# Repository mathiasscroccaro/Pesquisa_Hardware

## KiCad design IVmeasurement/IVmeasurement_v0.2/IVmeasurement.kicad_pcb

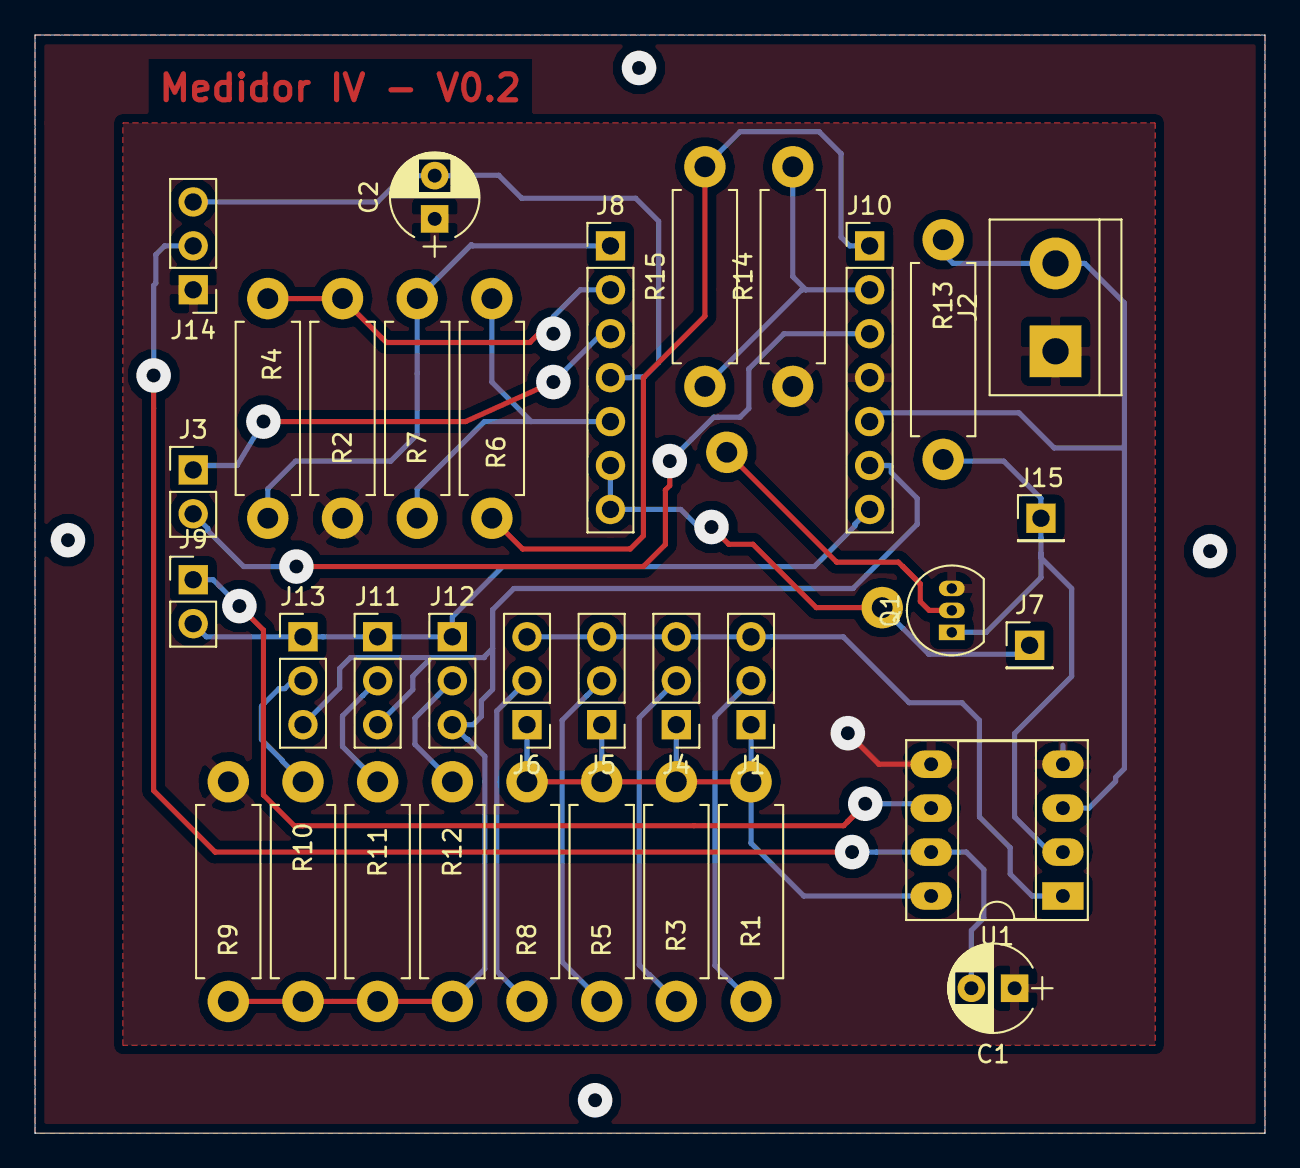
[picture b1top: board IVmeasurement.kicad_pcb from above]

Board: 2 copper layers, 71.1 x 63.5 mm, 35 parts (1 on the bottom side), 26 nets.

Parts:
C1, C2: 100nF; CP_Radial_D5.0mm_P2.50mm
J1, J4, J5, J6, J11, J12, J13: Conn_01x03; Pin_Header_Straight_1x03_Pitch2.54mm
J2: Sollar Cell; TerminalBlock_bornier-2_P5.08mm
J3: DAC; Pin_Header_Straight_1x02_Pitch2.54mm
J7: Test VGS; Pin_Header_Straight_1x01_Pitch2.54mm
J8, J10: Conn_01x07; Pin_Header_Straight_1x07_Pitch2.54mm
J9: ADC; Pin_Header_Straight_1x02_Pitch2.54mm
J14: Source; Pin_Header_Straight_1x03_Pitch2.54mm
J15: Test VDS; Pin_Header_Straight_1x01_Pitch2.54mm
Q1: BS170; TO-92_Inline_Narrow_Oval
R1, R6: 1M; R_Axial_DIN0411_L9.9mm_D3.6mm_P12.70mm_Horizontal
R2, R7, R14: 100k; R_Axial_DIN0411_L9.9mm_D3.6mm_P12.70mm_Horizontal
R3: 7.1k; R_Axial_DIN0411_L9.9mm_D3.6mm_P12.70mm_Horizontal
R4, R15: 51k; R_Axial_DIN0411_L9.9mm_D3.6mm_P12.70mm_Horizontal
R5: 609; R_Axial_DIN0411_L9.9mm_D3.6mm_P12.70mm_Horizontal
R8: 60; R_Axial_DIN0411_L9.9mm_D3.6mm_P12.70mm_Horizontal
R9: 10k; R_Axial_DIN0411_L9.9mm_D3.6mm_P12.70mm_Horizontal
R10: 23k; R_Axial_DIN0411_L9.9mm_D3.6mm_P12.70mm_Horizontal
R11: 320k; R_Axial_DIN0411_L9.9mm_D3.6mm_P12.70mm_Horizontal
R12: 100; R_Axial_DIN0411_L9.9mm_D3.6mm_P12.70mm_Horizontal
R13: R; R_Axial_DIN0411_L9.9mm_D3.6mm_P12.70mm_Horizontal
R16: 1k; R_Axial_DIN0411_L9.9mm_D3.6mm_P12.70mm_Horizontal
U1: INA128; DIP-8_W7.62mm_Socket_LongPads

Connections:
+1: J3.1, J8.3
+2: J8.5, R6.2, R7.1
+3: J2.2, J10.5, R13.1, U1.3
+3V3: C1.2, J14.2, U1.7
+4: J3.2, J10.3
+5V: C2.2, J8.4, J14.3
-1: J8.2, R2.2, R4.1
-2: J7.1, J8.6, J8.7, R16.2
-3: J10.6, J11.3, J12.3, J13.3, R9.2, R10.1, R11.1, R12.1
-4: J10.2, R14.2, R15.1
ADC1: J9.1, U1.6
ADC2: J9.2, J10.7, J11.1, J12.1, J13.1
unnamed: J1.1, J4.1, J5.1, J6.1, R1.2, R3.2, R5.2, R8.2, U1.8
unnamed: J1.2, R1.1
unnamed: J1.3, J4.3, J5.3, J6.3, U1.1
unnamed: J4.2, R3.1
unnamed: J5.2, R5.1
unnamed: J6.2, R8.1
unnamed: J11.2, R11.2
unnamed: J12.2, R12.2
unnamed: J13.2, R10.2
unnamed: J15.1, Q1.1, R13.2, U1.2
Out1: J8.1, R4.2, R7.2
Out4: J10.1, R6.1, R15.2
SollarCell-: C1.1, C2.1, J2.1, J10.4, J14.1, Q1.3, R2.1, R9.1, R14.1, U1.4, U1.5
Vgs: Q1.2, R16.1
